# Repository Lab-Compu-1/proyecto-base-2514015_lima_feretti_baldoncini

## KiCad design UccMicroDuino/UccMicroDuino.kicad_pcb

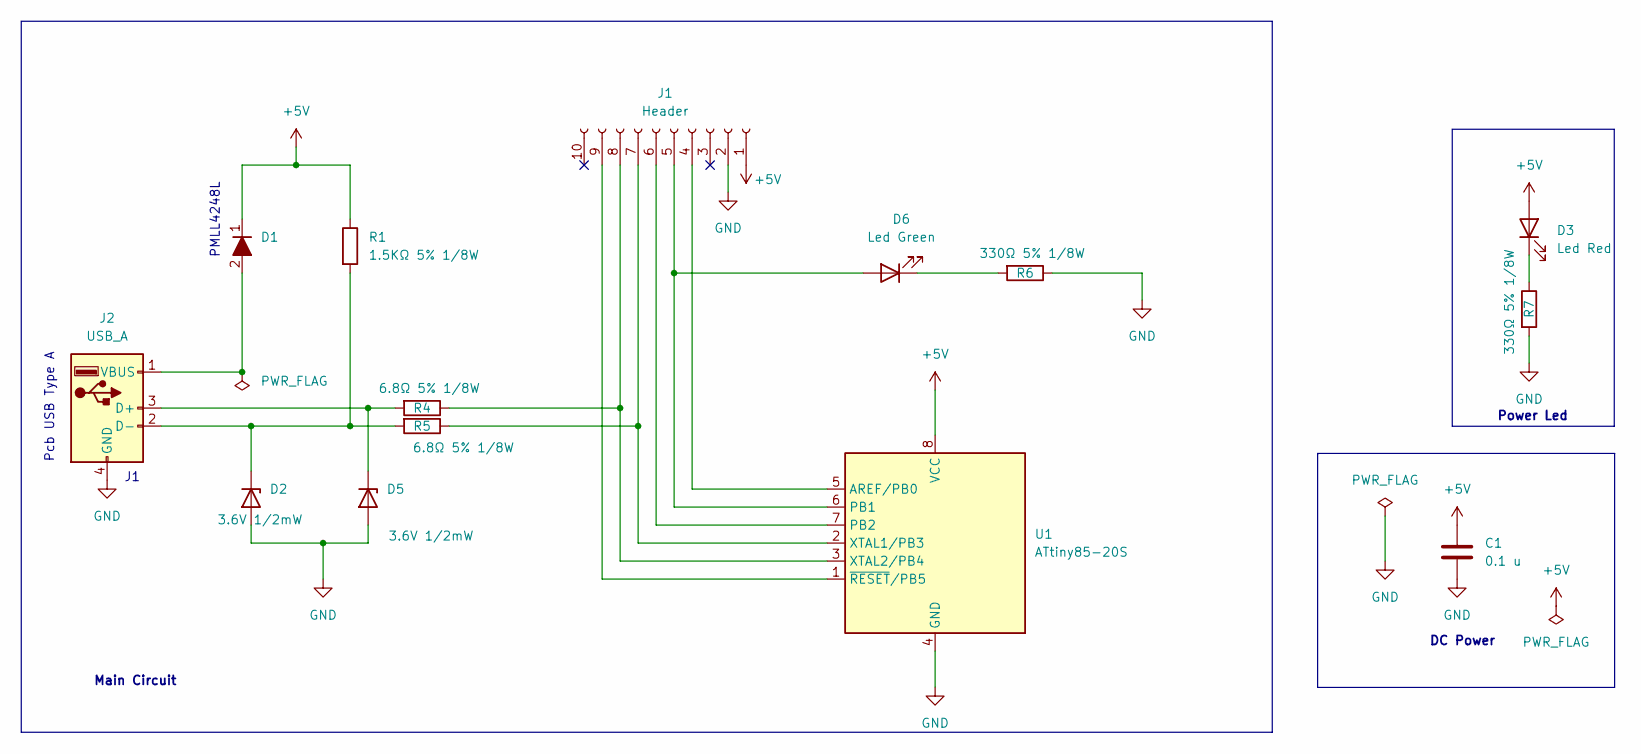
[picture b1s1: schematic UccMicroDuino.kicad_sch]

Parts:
C1: 0.1 u; C_0805_2012Metric_Pad1.18x1.45mm_HandSolder
D1: D_Filled; D_MiniMELF
D2, D5: 3.6V 1/2mW; D_SOD-123
D3: Led Red; ledSMD
D6: Led Green; ledSMD
J1: Header; PinHeader_1x10_P2.54mm_Vertical
J2: USB_A; USB_A_UCC
R1: 1.5KΩ 5% 1/8W; R_0805_2012Metric_Pad1.20x1.40mm_HandSolder
R4, R5: 6.8Ω 5% 1/8W; R_0805_2012Metric_Pad1.20x1.40mm_HandSolder
R6, R7: 330Ω 5% 1/8W; R_0805_2012Metric_Pad1.20x1.40mm_HandSolder
U1: ATtiny85-20S; SOIC-8W_5.3x5.3mm_P1.27mm

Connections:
+5V: C1.1, D1.1 (K), D3.2 (A), J1.1, R1.1, U1.8 (VCC)
GND: C1.2, D2.2 (A), D5.2 (A), J1.2, J2.4 (GND), R6.1, R7.2, U1.4 (GND)
unnamed: D1.2 (A), J2.1 (VBUS)
unnamed: D2.1 (K), J2.2 (D-), R1.2, R5.2
unnamed: D3.1 (K), R7.1
unnamed: D5.1 (K), J2.3 (D+), R4.2
unnamed: D6.2 (A), J1.5, U1.6 (PB1)
unnamed: D6.1 (K), R6.2
unnamed: J1.4, U1.5 (AREF/PB0)
unnamed: J1.6, U1.7 (PB2)
unnamed: J1.7, R5.1, U1.2 (XTAL1/PB3)
unnamed: J1.8, R4.1, U1.3 (XTAL2/PB4)
unnamed: J1.9, U1.1 (~RESET/PB5)

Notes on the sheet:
PMLL4248L
Pcb USB Type A
Main Circuit
DC Power
Power Led

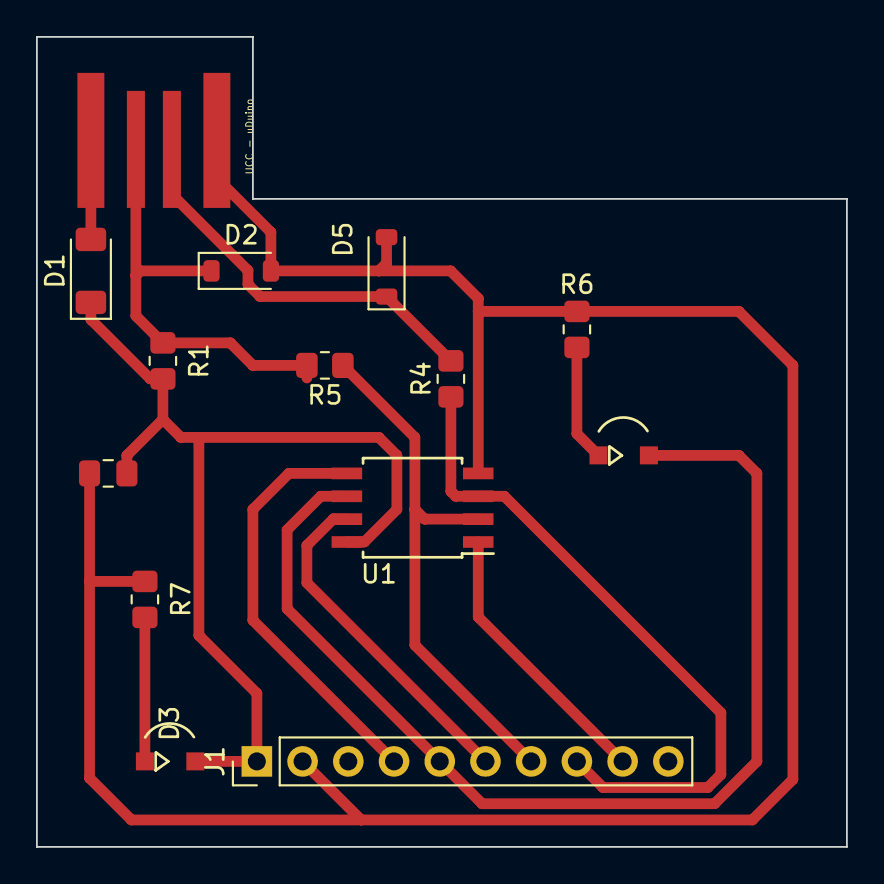
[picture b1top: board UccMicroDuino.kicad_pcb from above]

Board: 2 copper layers, 45.0 x 45.0 mm, 14 parts (0 on the bottom side), 13 nets.

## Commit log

2025-03-31 GitHub Classroom Feedback
2025-03-31 Setting up GitHub Classroom Feedback
2025-05-26 Primera Entrega
